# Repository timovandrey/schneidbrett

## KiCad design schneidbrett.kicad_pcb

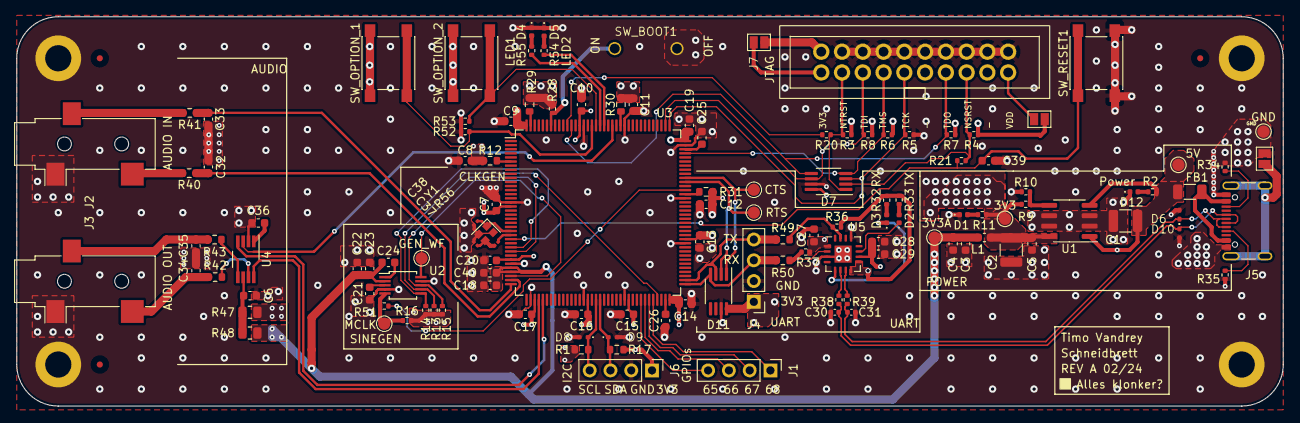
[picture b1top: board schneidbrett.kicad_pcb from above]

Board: 4 copper layers, 154.9 x 47.6 mm, 134 parts (0 on the bottom side), 79 nets.

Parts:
3V3: PWR_TP_3V3; TestPoint_Pad_D1.5mm
3V3A: PWR_TP_3V3A; TestPoint_Pad_D1.5mm
5V: PWR_TP_5V; TestPoint_Pad_D1.5mm
C1, C2: 22u; C_1210_3225Metric
C3, C18: 1u; C_0603_1608Metric
C4, C5, C6, C7, C8, C9, C10, C11, C12, C13, C14, C15, C16, C17, C19, C20, C21, C23, C27, C28, C39, C40: 100n; C_0603_1608Metric
C22, C36: 10u; C_0603_1608Metric
C24: 10n; C_0603_1608Metric
C25, C26: 2u2; C_0603_1608Metric
C29: 4u7; C_0603_1608Metric
C30, C31: 47p; C_0402_1005Metric
C32, C33, C34, C35: 500n; C_0603_1608Metric
C37, C38: 10p; C_0201_0603Metric
CTS: CTS_ACCESS_PT; TestPoint_Pad_D1.5mm
D1, D12: SML-LX0402UPGC-TR; LED_0402_1005Metric
D2: SML-LX0402SIC-TR; LED_0402_1005Metric
D3: SML-LX0402SOC-TR; LED_0402_1005Metric
D4, D5: SML-LX0402USBC-TR; LED_0402_1005Metric
D6, D8, D9, D10: TVSA04V05C006
D7, D11: DT6250-06MR-13; MSOP-8_3x3mm_P0.65mm
FB1: 100R; C_1206_3216Metric
FID1, FID2, FID3: Fiducial; Fiducial_0.75mm_Mask2.25mm
GEN_WF: TestPoint; TestPoint_Pad_D1.5mm
GND: PWR_TP_GND; TestPoint_Pad_D1.5mm
H1, H2, H3, H4: MountingHole_Pad; MountingHole_3.2mm_M3_DIN965_Pad
J1: GPIO_CONNECTOR; PinHeader_1x04_P2.54mm_Vertical
J2: Audio_Jack_Input; Jack_3.5mm_CUI_SJ-3523-SMT_Horizontal
J3: Audio_Jack_Output; Jack_3.5mm_CUI_SJ-3523-SMT_Horizontal
J4: UART_CONNECTOR; PinHeader_1x04_P2.54mm_Vertical
J5: USB_C_Receptacle_USB2.0; USB_C_Receptacle_GCT_USB4105-xx-A_16P_TopMnt_Horizontal
J6: I2C_CONNECTOR; PinHeader_1x04_P2.54mm_Vertical
J7: ST-LINK_V2_20Pin_Connector
L1: 27n; C_0603_1608Metric
MCLK: TestPoint; TestPoint_Pad_D1.5mm
R1, R17: 5k1; R_0603_1608Metric
R2, R11, R54, R55: 680R; R_0402_1005Metric
R3, R4, R5, R6, R7, R8, R13, R14, R15, R16, R52, R53: 4k7; R_0402_1005Metric
R9, R10, R20, R21, R51: 0R; R_0402_1005Metric
R12, R29, R30, R31: 0R; R_0603_1608Metric
R28, R34, R35, R36, R37: 5k1; R_0402_1005Metric
R32, R33: 270R; R_0402_1005Metric
R38, R39: 27R; R_0402_1005Metric
R40, R41, R42, R43: 10R; R_0603_1608Metric
R47, R48: 0R; R_0805_2012Metric
R49, R50: 100R; R_0603_1608Metric
R56: 0R; R_0201_0603Metric
RTS: RTS_ACCESS_PT; TestPoint_Pad_D1.5mm
SW_BOOT1: SW_DIP_x01; DS01-254-L-01BE
SW_OPTION_1, SW_OPTION_2: PTS645SM43SMTR92 LFS; SW_SPST_PTS645
SW_RESET1: PTS645SM43SMTR92 LFS; SW_SPST_PTS645
TCB2, TCB3: SolderJumper-2_P1.3mm_Open_Pad1.0x1.5mm
TCB4: USB_SHIELDING_BRIDGE; SolderJumper-2_P1.3mm_Open_Pad1.0x1.5mm
U1: MAX604CSA; SOIC-8_3.9x4.9mm_P1.27mm
U2: AD9833xRM; MSOP-10_3x3mm_P0.5mm
U3: STM32F767ZITx; LQFP-144_20x20mm_P0.5mm
U4: LM4881M; VSSOP-8_3.0x3.0mm_P0.65mm
U5: FT230XQ; QFN-16-1EP_4x4mm_P0.65mm_EP2.1x2.1mm
Y1: 25MHz; Crystal_SMD_2016-4Pin_2.0x1.6mm

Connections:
+3.3V: 3V3.1, C2.1, C5.1, C7.1, C8.1, C9.1, C10.1, C11.1, C12.1, C13.1, C14.1, C15.1, C16.1, C17.1, C19.1, C20.1, D7.8 (VCC), D11.8 (VCC), J4.1, J6.1, J7.1 (VREF), L1.1, R1.1, R3.2, R4.2, R6.2, R7.2, R8.2, R9.2, R11.2, R12.1, R13.2, R14.2, R15.2, R16.2, R17.1, R28.2, R29.1, R30.1, R31.1, R47.2, SW_OPTION_1.1, SW_OPTION_2.1, TCB2.1, TCB3.1, U1.8 (OUT), U3.17 (VDD), U3.30 (VDD), U3.39 (VDD), U3.52 (VDD), U3.62 (VDD), U3.72 (VDD), U3.84 (VDD), U3.108 (VDD), U3.131 (VDD), U3.144 (VDD)
+3.3VA: 3V3A.1, C3.1, C4.1, C18.1, C22.1, C23.1, C24.1, C40.1, L1.2, R48.2, U2.2 (VDD), U3.32 (VREF+), U3.33 (VDDA)
+5V: 5V.1, C1.1, C28.1, C29.1, FB1.2, R2.2, U1.1 (IN), U1.4 (~OFF), U5.10 (VCC)
+VCCIO_FTDI: C27.1, R32.2, R33.2, R36.2, R37.2, U5.1 (VCCIO), U5.8 (3V3OUT), U5.9 (~RESET)
/Analog/AUDIO_BYPASS: C36.1, U4.1 (BYPASS)
/Analog/AUDIO_PWR_JUNCTION: C6.1, R47.1, R48.1, U4.6 (VDD)
/Analog/GEN_CAP: C21.2, U2.3 (CAP/2.5V)
/Analog/GEN_COMP: C24.2, U2.1 (COMP)
/Analog/GEN_MCLK: MCLK.1, R16.1, R51.2, U2.5 (MCLK)
/Connectors/JTAG_NSRST_INNER: D7.2 (IO2), J7.15 (~SRST), R4.1, R21.1
/Connectors/JTAG_NTRST_INNER: D7.1 (IO1), J7.3 (~TRST), R3.1, R20.1
/Connectors/USB_CC1: J5.A5 (CC1), R35.1
/Connectors/USB_CC2: J5.B5 (CC2), R34.1
/Connectors/USB_SHIELDING: J5.S1 (SHIELD), TCB4.1
/Controller/GPIO_LED_1_JUNCTION: D4.2 (A), R55.1
/Controller/GPIO_LED_2_JUNCTION: D5.2 (A), R54.1
/Controller/MCU_BOOT0: R28.1, SW_BOOT1.2, U3.138 (BOOT0)
/Controller/MCU_CRYSTAL_3: C37.1, R56.1, Y1.3
/Controller/MCU_PDR_ON: R29.2, U3.143 (PDR_ON)
/Controller/MCU_VBAT: R12.2, U3.6 (VBAT)
/Controller/MCU_VDDSDMMC: R30.2, U3.121 (VDDSDMMC)
/Controller/MCU_VDDUSB: R31.2, U3.95 (VDDUSB)
/Peripherals/FTDI_CBUS1: D2.1 (K), U5.11 (CBUS1)
/Peripherals/FTDI_CBUS2: D3.1 (K), U5.5 (CBUS2)
/Peripherals/FTDI_LED1: D2.2 (A), R33.1
/Peripherals/FTDI_LED2: D3.2 (A), R32.1
/Power Supply/POWER_LED_3V3: D1.2 (A), R11.1
/Power Supply/POWER_LED_5V: D12.2 (A), R2.1
/Power Supply/POWER_SET_TERMINAL: R9.1, R10.2, U1.5 (SET)
Audio_In_Left: J2.T, R40.2
Audio_In_Left_Filtered: C32.1, R40.1, U3.35 (PA1)
Audio_In_Right: J2.R, R41.2
Audio_In_Right_Filtered: C33.1, R41.1, U3.36 (PA2)
Audio_Out_Left: R42.2, U4.7 (OUT_A)
Audio_Out_Left_Filtered: C34.1, J3.T, R42.1
Audio_Out_Left_MCU: U3.40 (PA4), U4.8 (IN_A)
Audio_Out_Right: R43.2, U4.5 (OUT_B)
Audio_Out_Right_Filtered: C35.1, J3.R, R43.1
Audio_Out_Right_MCU: U3.41 (PA5), U4.4 (IN_B)
Audio_Shutdown: U3.123 (PD7), U4.3 (SHUTDOWN)
FTDI_UART_RX: R37.1, R50.2, U5.2 (RXD)
FTDI_UART_TX: R36.1, R49.2, U5.15 (TXD)
FTDI_USBD+: R38.1, U5.6 (USBDP)
FTDI_USBD-: R39.1, U5.7 (USBDM)
GEN_REFCLK: R51.1, U3.96 (PC6)
GEN_SPI_CLK: R13.1, U2.7 (SCLK), U3.69 (PB10)
GEN_SPI_CSEL: R15.1, U2.8 (~FSYNC), U3.28 (PC2)
GEN_SPI_DATA: R14.1, U2.6 (SDATA), U3.27 (PC1)
GEN_WAVEFORM: GEN_WF.1, U2.10 (VOUT), U3.34 (PA0)
GND: C1.2, C2.2, C3.2, C4.2, C5.2, C6.2, C7.2, C8.2, C9.2, C10.2, C11.2, C12.2, C13.2, C14.2, C15.2, C16.2, C17.2, C18.2, C19.2, C20.2, C21.1, C22.2, C23.2, C25.2, C26.2, C27.2, C28.2, C29.2, C30.2, C31.2, C32.2, C33.2, C34.2, C35.2, C36.2, C37.2, C38.2, C39.2, C40.2, D1.1 (K), D4.1 (K), D5.1 (K), D6.1, D7.7 (VSS), D8.1, D9.1, D10.1, D11.7 (VSS), D12.1 (K), GND.1, H1.1, H2.1, H3.1, H4.1, J2.S, J3.S, J4.2, J5.A1 (GND), J5.A12 (GND), J5.B1 (GND), J5.B12 (GND), J6.2, J7.4 (GND), J7.6 (GND), J7.8 (GND), J7.10 (GND), J7.12 (GND), J7.14 (GND), J7.16 (GND), J7.18 (GND), J7.20 (GND), R5.1, R10.1, R34.2, R35.2, R52.1, R53.1, SW_BOOT1.1, SW_RESET1.2, TCB4.2, U1.2 (GND), U1.3 (GND), U1.6 (GND), U1.7 (GND), U2.4 (DGND), U2.9 (AGND), U3.16 (VSS), U3.31 (VSSA), U3.38 (VSS), U3.51 (VSS), U3.61 (VSS), U3.83 (VSS), U3.94 (VSS), U3.107 (VSS), U3.120 (VSS), U3.130 (VSS), U4.2 (GND), U5.3 (GND), U5.13 (GND), U5.17 (GND), Y1.2, Y1.4
GPIO_BTN_1: R52.2, SW_OPTION_1.2, U3.128 (PG13)
GPIO_BTN_2: R53.2, SW_OPTION_2.2, U3.127 (PG12)
GPIO_LED_1: R55.2, U3.126 (PG11)
GPIO_LED_2: R54.2, U3.125 (PG10)
GPIO_OPT_0: J1.4, U3.65 (PE12)
GPIO_OPT_1: J1.3, U3.66 (PE13)
GPIO_OPT_2: J1.2, U3.67 (PE14)
GPIO_OPT_3: J1.1, U3.68 (PE15)
JTAG_NSRST: C39.1, R21.2, SW_RESET1.1, U3.25 (NRST)
JTAG_NTRST: R20.2, U3.134 (PB4)
JTAG_TCK: D7.3 (IO3), J7.9 (TCK/SWCLK), R5.2, U3.109 (PA14)
JTAG_TDI: D7.6 (IO6), J7.5 (TDI), R8.1, U3.110 (PA15)
JTAG_TDO: D7.5 (IO5), J7.13 (TDO/SWO), R7.1, U3.133 (PB3)
JTAG_TMS: D7.4 (IO4), J7.7 (TMS/SWDIO), R6.1, U3.105 (PA13)
MCU_CRYSTAL_PH0: C38.1, U3.23 (PH0), Y1.1
MCU_CRYSTAL_PH1: R56.2, U3.24 (PH1)
MCU_I2C_SCL: D8.2, J6.4, R1.2, U3.54 (PF14)
MCU_I2C_SDA: D9.2, J6.3, R17.2, U3.55 (PF15)
MCU_UART_CTS: CTS.1, D11.1 (IO1), U3.99 (PC9)
MCU_UART_RTS: D11.2 (IO2), RTS.1, U3.98 (PC8)
MCU_UART_RX: D11.4 (IO4), J4.3, R50.1, U3.73 (PB12)
MCU_UART_TX: D11.3 (IO3), J4.4, R49.1, U3.74 (PB13)
unnamed: J7.2 (VAPP), TCB2.2
unnamed: J7.19 (VDD), TCB3.2
unnamed: C26.1, U3.71 (VCAP_1)
unnamed: C25.1, U3.106 (VCAP_2)
USB+: C30.1, D10.2, J5.A6 (D+), J5.B6 (D+), R38.2
USB-: C31.1, D6.2, J5.A7 (D-), J5.B7 (D-), R39.2
VBUS: FB1.1, J5.A4 (VBUS), J5.A9 (VBUS), J5.B4 (VBUS), J5.B9 (VBUS)

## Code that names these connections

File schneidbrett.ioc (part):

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Mcu.Name=STM32F767ZITx
Mcu.Package=LQFP144
Mcu.UserName=STM32F767ZITx
PA0/WKUP.GPIOParameters=GPIO_Label
PA0/WKUP.GPIO_Label=GEN_INPUT
PA0/WKUP.Signal=ADCx_IN0
PA1.GPIOParameters=GPIO_Label
PA1.GPIO_Label=AUDIO_IN_LEFT
PA1.Signal=ADCx_IN1
PA13.Mode=JTAG_5_pins
PA13.Signal=SYS_JTMS-SWDIO
PA14.Mode=JTAG_5_pins
PA14.Signal=SYS_JTCK-SWCLK
PA15.Mode=JTAG_5_pins
PA15.Signal=SYS_JTDI
PA2.GPIOParameters=GPIO_Label
PA2.GPIO_Label=AUDIO_IN_RIGHT
PA2.Signal=ADCx_IN2
PA4.GPIOParameters=GPIO_Label
PA4.GPIO_Label=AUDIO_OUT_LEFT
PA4.Signal=COMP_DAC1_group
PA5.GPIOParameters=GPIO_Label
PA5.GPIO_Label=AUDIO_OUT_RIGHT
PA5.Signal=COMP_DAC2_group
PB10.Mode=TX_Only_Simplex_Unidirect_Master
PB10.Signal=SPI2_SCK
PB12.Mode=Asynchronous
PB12.Signal=UART5_RX
PB13.Mode=Asynchronous
PB13.Signal=UART5_TX
PB3.Mode=JTAG_5_pins
PB3.Signal=SYS_JTDO-SWO
PB4.Mode=JTAG_5_pins
PB4.Signal=SYS_JTRST
PC1.Mode=TX_Only_Simplex_Unidirect_Master
PC1.Signal=SPI2_MOSI
PC2.GPIOParameters=GPIO_Label
PC2.GPIO_Label=SPI2_CSEL
PC2.Signal=GPIO_Output
PC6.Signal=S_TIM8_CH1
PC8.Mode=CTS_RTS
PC8.Signal=UART5_RTS
PC9.Mode=CTS_RTS
PC9.Signal=UART5_CTS
PD7.GPIOParameters=GPIO_Label
PD7.GPIO_Label=AUDIO_MUTE
PD7.Signal=GPIO_Output
PE12.Signal=GPIO_Input
PE13.Signal=GPIO_Input
PE14.Signal=GPIO_Input
PE15.Signal=GPIO_Input
PF14.Mode=I2C
PF14.Signal=I2C4_SCL
PF15.Mode=I2C
PF15.Signal=I2C4_SDA
PG10.GPIOParameters=GPIO_Label
PG10.GPIO_Label=LED2
PG10.Signal=GPIO_Output
PG11.GPIOParameters=GPIO_Label
PG11.GPIO_Label=LED1
PG11.Signal=GPIO_Output
PG12.GPIOParameters=GPIO_Label
PG12.GPIO_Label=BTN2
PG12.Signal=GPIO_Input
PG13.GPIOParameters=GPIO_Label
PG13.GPIO_Label=BTN1
PG13.Signal=GPIO_Input
RCC.HSE_VALUE=25000000
board=custom

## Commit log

2024-01-08 Added ESD, updated Footprints, BOM, etc.
2024-01-13 Schematic is done for now, starting layout
2024-01-14 Layout done, footprints mostly assigned, 3D models assigned if not annoying to get. Few TODOs left and they are marked on the PCB.
2024-01-16 Board outline finished, component placement, added markers, added annotations, etc.
2024-01-23 Layout and routing basically done, check again before delivering
2024-02-04 Routing, Zone fillings, stitching vias, etc.
    - Routing is now done, unconnected pads are connected now
    - Ground pour on top and bottom layer; other zones were changed for
    compliance
    - Other routing and connections
    - Stitching vias
    - Other minor changes
2024-02-04 Final finish
    - Added silkscreen notes
    - Updated FTDI chip datasheet link
    - Added BOM, Gerber-Files
    - Added (coarse) calculation sheet for parts
    - Minor changes, maybe
2024-02-12 Added voltage ratings for capacitors
2024-02-12 Added capacitor voltage rating
2024-09-21 Create LICENSE
